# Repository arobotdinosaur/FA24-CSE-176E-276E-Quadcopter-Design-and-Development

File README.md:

Quadcopters designed by Kaustubh Kanagalekar and Alexander Haken

## Introduction

In this project class, we were challenged to design a printed circuit board (PCB) quadcopter and program it using Arduino software in order to achieve flight. 

The class was broken into multiple smaller milestones- PCB design for electronic components, PCB design for quadcopter, sensor filtering and calibration, Proportional, Integral, Derivative (PID) tuning, PCB quadcopter assembly, and flight. As we were designing the PCB quadcopter using computer software, we were provided with a test flight control board (FCB) that we could work on concurrently. We could use either the FCB or the custom PCB quadcopter for demonstration purposes. 

The skills that we learned from the class were-
1. PCB design and fabrication
2. Embedded systems programming 
3. Control theory and sensor calibration 

## Electronic Design

Using Fusion 360, we were tasked with designing the following components from scratch- 

1. Resistor (0805 0Ohm) 
2. Red LED 
3. MOSFET (N-channel) 
4. Inertial measurement unit (IMU) (LSM6DSOXTR 6-Axis) 

We referenced the data sheets for each component online and extensively studied the footprints. 
More specifically, we utilised the footprints tab in Fusion 360 to add SMD pads, silkscreens, keepouts, etc. to accurately replicate the dimensions. 

We also took advantage of the automated building tool at times to accurately build the electronic components.  

Footprint of the resistor

Footprint of the LED 

Footprint of the MOSFET 

Footprint of the IMU 

After creating the footprints, we built symbols for each electronic component using the standard IEEE styling conventions using the symbols tab. 

Finally, we connected the footprints and the symbols of each component in the components tab so that we could use them in our quadcopter schematic and design. 

We ensured that we met all the necessary guidelines and requirements set forth by the PCB manufacturer and instructor in our designs.  

## Quadcopter Design 

We were tasked with creating the schematic for the PCB quadcopter. In addition to our custom made components, we were also provided with additional parts from the instructor. 
The quadcopter had multiple smaller sketches- 
1. The microcontroller connections  
2. Bootloader 
3. IMU 
4. Debug/Rescue Header 
5. Motor Driver 
6. Netbridge and power supply 

### Microcontroller connections
We connected various pins and components to the microcontroller. The most significant connection we had was the balun (used for allowing balanced and unbalanced lines to be interfaced without major disturbances in impedances). This was significant as it allowed us to securely connect the antenna in our design. We were deliberate in our antenna placement as incorrect placements would yield spotty data transmission, and the quadcopter may not be able to fly.  

### Bootloader 
The primary objective of including the bootloader was  to load code to the microcontroller. Pins were connected to the microcontroller from the bootloader. 

### IMU 
We established a communication protocol with the microcontroller using I2C (Inter-Integrated Circuit). We incorporated two wires (Serial Data Line and Serial Clock Line) to transmit data between the microcontroller and IMU. 

### Debug/Rescue Header 
The rescue header was incorporated in order to help with debugging signals during testing. We also added a IMU reuse header in case our soldered IMU had issues. 

### Motor Driver 
We built four copies of the motor driver sketch as there were four motors driving the quadcopter. We included motor pads, mosfets, and a diode in the sketch. More importantly, we also included a decoupling capacitor to help absorb switching noise from the motors.

### Netbridge and Power Supply 
We designed a low-dropout voltage regulator in the schematic to provide a stable power output of 3V to the motors. This was because the batteries were providing power ranging from 4V to 5V. We had two power rails: An unregulated power rail (called VBAT) that provides power to the motors and input of the voltage regulator and is driven directly by the battery, and a regulated supply driven by the voltage regulator (called 3V) 

A netbridge was also created in order to electrically connect two nets in a schematic while keeping the nets separate in schematic . This was done to connect digital ground (BAT_GND) to regular ground. 

Image of the overall schematic 

### PCB Design 
We created a custom shape for the quadcopter and placed all the necessary components from the sketch to the board. The placement of some components were extremely important- for example, the antenna had to be placed near the edge of the board for uninterrupted communication, and the IMU had to be placed at the centre for accurate measurements. The crystal was placed close to the microcontroller, and the motor controllers were placed at the edges of the board. 

We primarily used the autorouter to route all wirings and connections, except in the case of the antenna and parts of the microcontroller. The antenna had to be connected with a large wire (50 mm) manually to the balun and other components (such as the corresponding  microcontroller pins and capacitors). The crystal also had to manually routed with specific pins of the microcontroller. We utilized differential pairs for sending the signals from the antenna and crystal back to the microcontroller due to the sensitivity of these components.

The board had to fit under a 13.9 cm square requirement  with motor holes of 12.2 mm for optimal placement. 
In Fusion 360, the board was aligned to a 1 mm grid for aesthetic reasons. 

We had four layers on the board in order to manage all the wirings and connections succinctly. We had a top layer, bottom layer, and two internal layers (one for 3V/VBAT and the other for GND/BAT_GND). The top and bottom layers involved signal routing for connecting various electronic components. The bottom plan was used whenever possible to reduce electrical noise. The 3V/VBAT and GND/BAT_GND layers were exclusively used for delivering power and ground signals, respectively. The traces that carried both power and ground signals were as short as possible to provide a low-resistance path for current to flow. 
We took care to leave a gap in all the layers beneath the IMU as the manufacture specified that we should not have metal underneath it for best performance.
 
Image of the connected boards in Fusion 360.

## Sensor Filtering and Calibration 

Prior to reading data from the IMU, we had to establish a connection between a test remote and the FCB; we accomplished this using a check-sum that would transmit data sent from the remote (such as throttle value, pitch, roll, yaw) to the FCB. In addition, we also wrote code that read the existing gimbal value from the remote and transmitted it to the FCB to achieve flight. 
The check-sum was created in order to prevent bad data packets from getting sent over and to only accept packets that were sent from our remote (and not from other groups). 

On the FCB, we had to read data from the IMU to accurately measure the orientation. We used an existing library corresponding to the IMU called Adafruit_AHRS- from this, we used the `Adafruit_Simple_AHRS::getQuadOrientation()` function to gather all the necessary data.
We obtained the pitch rate, roll, and yaw from the quad orientation function.  
After gathering these data from the IMU, we created a complementary filter to filter out some of the noise created by the accelerometer and gyroscope. The accelerometer (Euler angles of the orientation) and gyroscope readings (the angular accelerations) were taken from the IMU. 
The reason we created a complementary filter was to gather the best possible data from both the gyroscope and the accelerometer as each inertial sensor has positives and drawbacks. The accelerometers do not drift over time, but they are quite noisy when the motors are running, and slightly less responsive compared to the gyroscope. Whereas, gyroscopes are less noisy than  the accelerometers, but the resulting measurement will drift over time due to accumulated error. We tried to set a high gain such that we could extract more data from the gyroscope in our code. 
We used a standard formula shown below with a gain of 0.98- `cf_angle = (gain) * (cf_angle + (gyro_raw * RAD_TO_DEG * dt)) + (1-gain) * (acc_angle)`

`RAD_TO_DEG = 57.295779513082320876798154814105`
`cf_angle` is the angle resulted from the complementary  filter, `gyro_raw` is the gyroscope measurement, `acc_angle` is the Euler angles, `dt` is the change in time from the measurements.  

We also accounted for any offsets caused by the IMU in the code to have it read zero when levelled. 
We only performed complementary filtering on the roll and pitch axes. 

## PID Control and Tuning 
PID is a type of controller used in feedback systems to regulate speed, position, and various other parameters to ensure stability. We used PID to keep the FCB stable and levelled when the motors were running. 
Proportional (P) responds to the current error and provides immediate action 
Integral (I) accumulates past errors 
Derivative (D) predicts future errors based on the rate of change. 
This was implemented for the pitch and roll axes using the following equation- 
`PID = (Kp* error) + Ki* integral - Kd* derivative` 
Where `Kp, Ki, Kd` are constants that are determined by testing, `error` is the difference from the remote gimbal input and the offset of the axis (`error = setpoint - corrected`), `integral` is `integral = error* dt+integral` , and derivative is the raw gyro readings in degrees. We used the raw gyro readings rather than doing a numerical derivative of cf_pitch because the raw gyroscope readings had slightly less delay. 

PID for yaw rate was implemented a bit differently. The control was only proportional to on the velocity error in yaw, which we got directly from the raw gyroscope yaw data.

After writing the code for all three axes control, we combined them so that there would be an equal output to the motors. We implemented a mixing function which increased the power for the front motors and decreased the power for the rear motors based on the PID output.

Through trial and error, we were able to find the optimal `Kp, Ki, Kd` values for the various axes to achieve stability. For pitch and roll: a ‘P’ overshoot would have resulted in the FCB “sway” from one end to another, an ‘I’ overshoot would have resulted in levelling at an odd angle, and a ‘D’ overshoot would have resulted in the FCB oscillating rapidly. Undershoots of each would have resulted in the quad not being able to move at all. For yaw rate, overshoots of ‘P’ and ‘D’ resulted in the FCB spinning uncontrollably in space, whereas undershoots would have not caused any motion. 

One critical factor for having reliable PID control was having a fast control loop running on the microcontroller. We initially had issues with "derivative kick" where the derivative term was causing unstable behavior due to a high control latency. To optimize speed, we made sure that only critical processes were running. Once we commented out all the print statements that we'd been using for debugging, the loop time reduced from about 35 ms to only 8 ms, and our PID controller ran much better.

For determining the yaw rate coefficients, our control was proportional to the yaw rate error (thus we did not have a `Kd` value after testing).  

This is a video of the PID demonstration for the pitch axis

## PCB Assembly 
After our PCB quadcopter boards were manufactured, we started on the assembly portion of the board. We applied solder paste to our boards using a stencil (a thin aluminium sheet with precise holes corresponding to the board). Immediately after, we attached all the necessary electronic components by hand, ensuring accuracy and precision. We later used a reflow oven to connect the components and the PCB pads as a reflow oven guarantees a secure connections between the paste applied to the PCB pads and the attached components. 
 
Picture of assembly after reflow (note that some components were missing due to unavailability at the time of assembly) 

## Flight 
We demonstrated flight using the provided FCB. 

Flight was broken into the following categories- 
1. "Roombaing" -- moving around the the floor with dowels installed with direction control and minimal yaw
2. Repeated, vertical hopping (>1 inches, > 0.25 second)
3. Repeated, vertical hopping (>6 inches, > 1 second)
4. Repeated, vertical hopping (>12 inches, > 3 seconds)
5. Short flight (>12 inches, > 6 seconds)
6. Sustained flight (> 12 inches, > 10 seconds, demonstrate yaw control)
7. 	Sustained flight (Fly long enough to consume an entire battery)

In this phase, we had also implemented a “trimming” mechanism where we would manually offset any discrepancies in pitch and roll to ensure a level flight takeoff. We would test which direction the FCB would travel towards when throttle was applied and would adjust any errors according. Trimming would have to be done every time we flew from a different location as ground would be levelled differently at each location. 

In our final demonstration, we were able to achieve FL 5. 

Please download the video after clicking the "?" icon to view the flight

## Acknowledgements
We would like to thank our instructor, Dr. Steven Swanson, our TA, Zifeng Zhang, and our classmates for their assistance and guidance with the project.  
Here is the [link](https://github.com/NVSL/QuadClass-Resources) to the main quadcopter class repository.

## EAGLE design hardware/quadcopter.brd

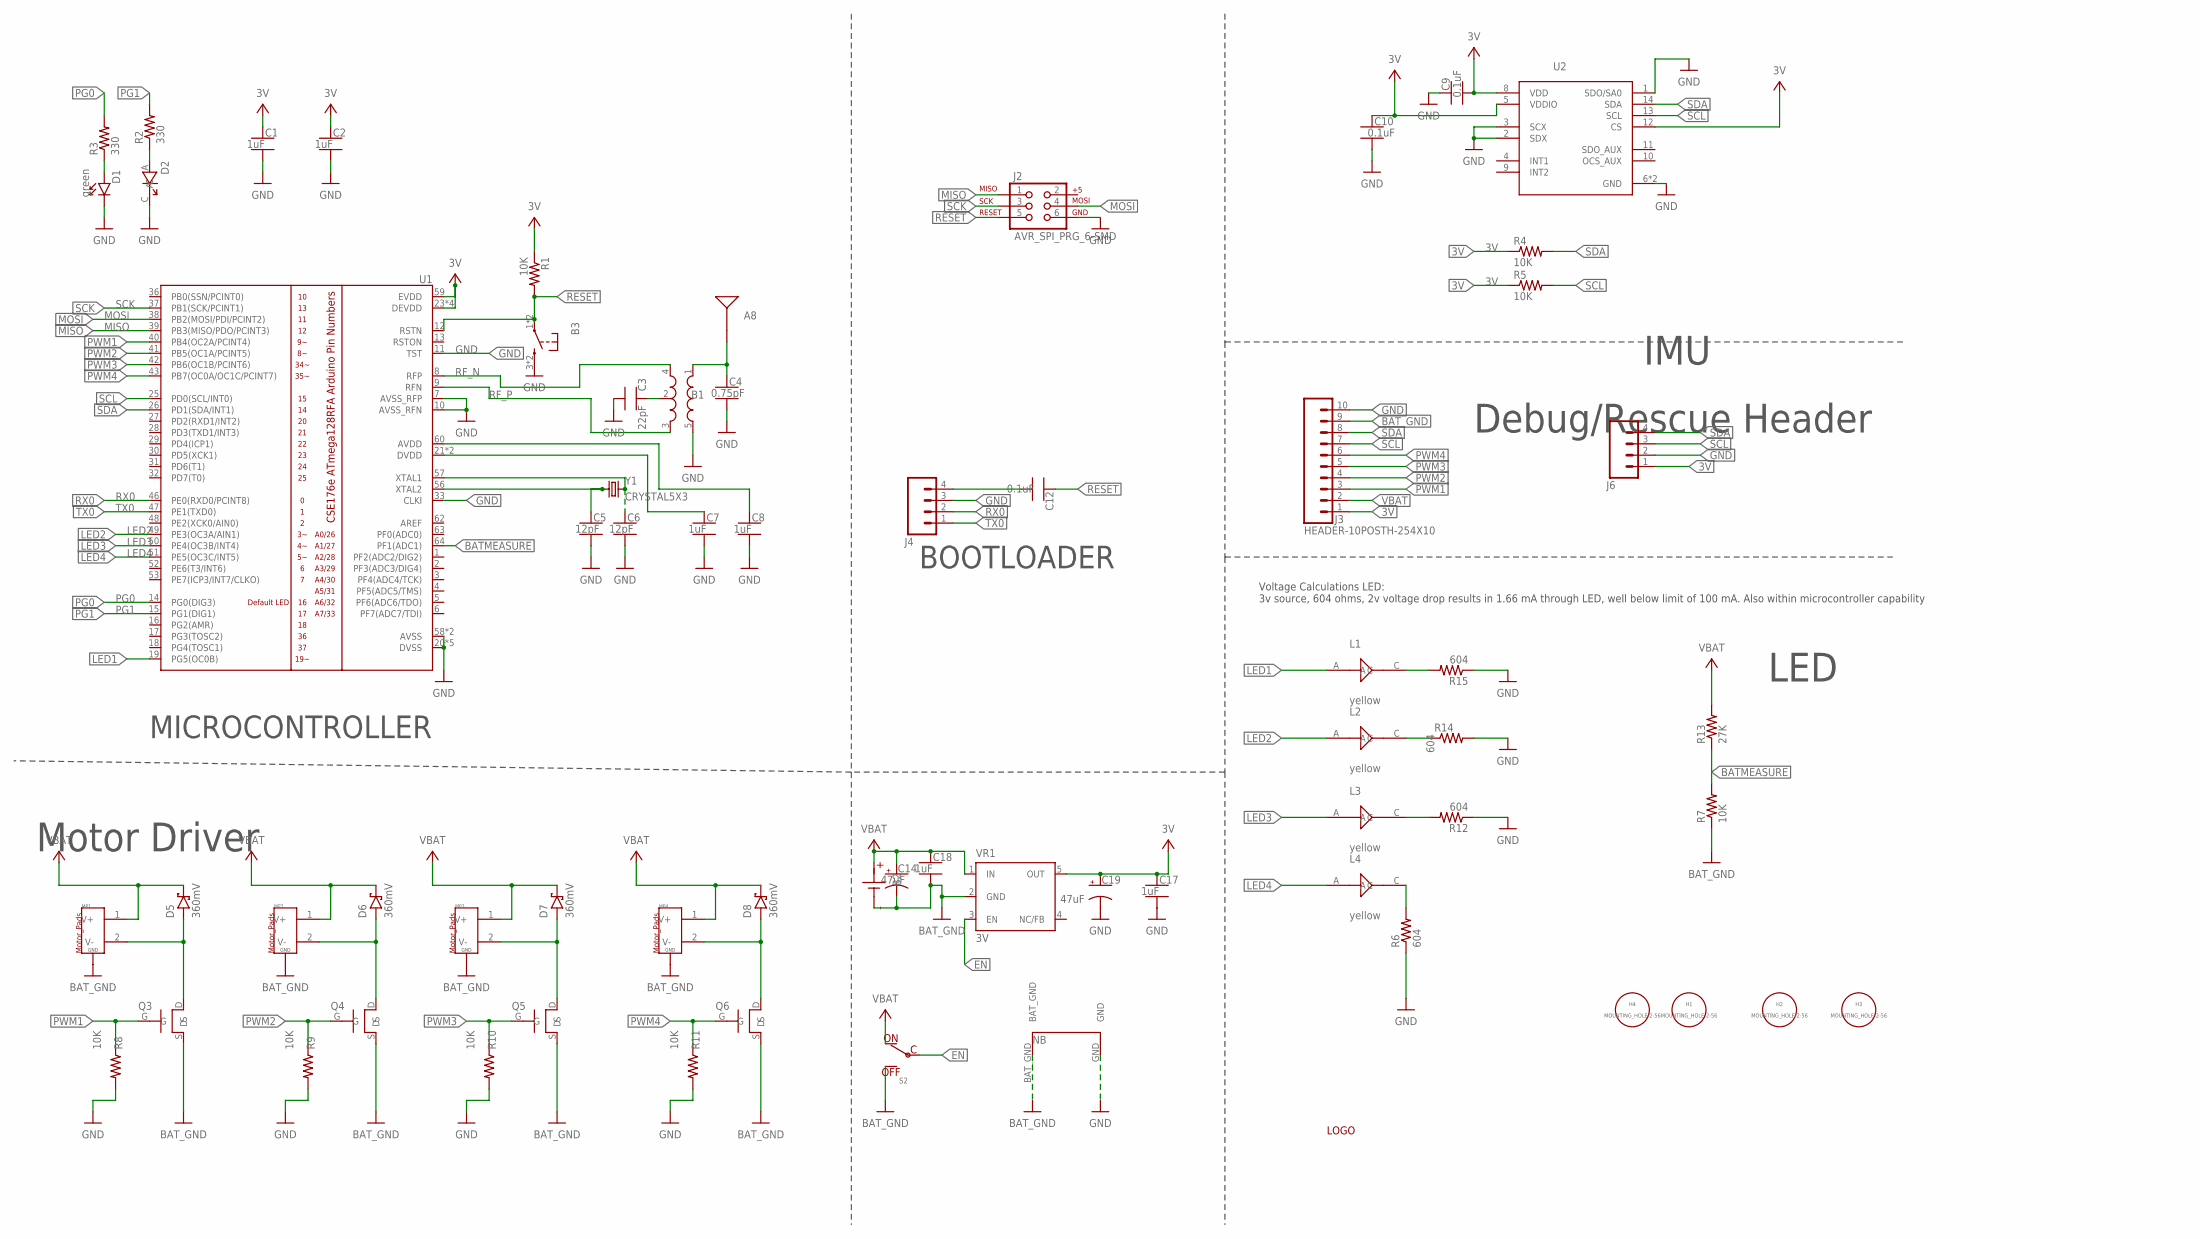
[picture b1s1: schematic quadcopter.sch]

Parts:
A8: ANTENNA-BOARD; ANT_PCB_2.4GHZ_NRF8001_1.6MM_1OZ
B1: BALUN0805; BALUN
B2: BATTERY-SCREW-TERMINAL; SCREW-TERMINAL-1X2-2.54MM
B3: PUSHBUTTON_SMD-VERTICAL-1; TE_FSM8JSMA_HS
C1, C2, C7, C8, C17, C18: 1uF; CAPC2012X140_HS
C3: 22pF; CAPC2012X140_HS
C4: 0.75pF; CAPC2012X140_HS
C5, C6: 12pF; CAPC2012X140_HS
C9, C10, C12: 0.1uF; CAPC2012X140_HS
C14, C19: 47uF; CAPMP3216X180
D1: green; LEDSC125X200X120-2_HS
D2: LED-RED-160-1178-1-ND; LED_160-1178-1-ND
D5, D6, D7, D8: 360mV; SODFL3516X96
H1, H2, H3, H4: MOUNTING_HOLE-2-56; 2-56-MOUNTING-HOLE-NO-METAL
J2: AVR_SPI_PRG_6-SMD; 2X3-SMD
J3: HEADER-10POSTH-254X10; HDRV10W63P254_10X1_2540X254H838_HS
J4: HEADER-4POS-0.1IN-FEMALE-SMD-BOTTOM-ENTRY; HEADER-1X4-BOTTOM-ENTRY
J6: HEADER-4POS-0.1IN-FEMALE; HDRVR4W80P254_1X4_1066X254X850B
L1, L2, L3, L4: yellow; LEDC1507X80NYELLOW
LOGO: PIDLOGO
MP1, MP2, MP3, MP4: MOTOR_PADS_GND-MOLEX-SMD; MOLEX-0532610271
NB: NETBRIDGE
Q3, Q4, Q5, Q6: MOSFET-FET-SI2302CDS-T1-E3CT-NDSI2302CDS-T1-E3CT-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; MOSFET_FET_SI2302CDS-T1-E3CT-ND
R1, R4, R5, R7, R8, R9, R10, R11: 10K; RESC2012X60_HS
R2, R3: 330; RESC2012X60_HS
R6, R12, R14, R15: 604; RESC2012X60_HS
R13: 27K; RESC2012X60_HS
S2: POWER-SWITCH-MFS201N-9-Z-SMD-EDGE; JS102011SAQN
U1: ATMEGA128RFA1; QFN-64
U2: IMU-LSM6DSOXTR-497-18367-1-ND497-18367-1-ND; LSM6DS0
VR1: 3V; SOT23-DBV
Y1: CRYSTAL5X3; CRYSTAL-SMD-5X3

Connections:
3V: C1.1, C2.1, C9.2, C10.1, C17.1, C19.1 (+), J3.1, J6.1, R1.1, R4.1, R5.1, U1.23 (DEVDD), U1.34 (DEVDD), U1.44 (DEVDD), U1.54 (DEVDD), U1.59 (EVDD), U2.5 (VDDIO), U2.8 (VDD), U2.12 (CS), VR1.5 (OUT)
BATMEASURE: R7.2, R13.1, U1.64 (PF1(ADC1))
BAT_GND: B2.1 (N), C14.2 (-), C18.2, J3.9, MP1.G1 (GND), MP1.G2 (GND), MP2.G1 (GND), MP2.G2 (GND), MP3.G1 (GND), MP3.G2 (GND), MP4.G1 (GND), MP4.G2 (GND), NB.BAT_GND, Q3.S, Q4.S, Q5.S, Q6.S, R7.1, S2.A (OFF), VR1.2 (GND)
EN: S2.C, VR1.3 (EN)
GND: B1.5 (GND), B3.3 (2), B3.4 (2), C1.2, C2.2, C3.2, C4.2, C5.2, C6.2, C7.2, C8.2, C9.1, C10.2, C17.2, C19.2 (-), D1.C, D2.C, J2.6, J3.10, J4.3, J6.2, NB.GND, R6.1, R8.2, R9.2, R10.2, R11.2, R12.1, R14.2, R15.1, U1.7 (AVSS_RFP), U1.10 (AVSS_RFN), U1.11 (TST), U1.20 (DVSS), U1.24 (DVSS), U1.33 (CLKI), U1.35 (DVSS), U1.45 (DVSS), U1.55 (DVSS), U1.58 (AVSS), U1.61 (AVSS), U2.1 (SDO/SA0), U2.2 (SDX), U2.3 (SCX), U2.6 (GND), U2.7 (GND)
LED1: L1.A, U1.19 (PG5(OC0B))
LED2: L2.A, U1.49 (PE3(OC3A/AIN1))
LED3: L3.A, U1.50 (PE4(OC3B/INT4))
LED4: L4.A, U1.51 (PE5(OC3C/INT5))
MISO: J2.1, U1.39 (PB3(MISO/PDO/PCINT3))
MOSI: J2.4, U1.38 (PB2(MOSI/PDI/PCINT2))
unnamed: D1.A, R3.1
unnamed: D2.A, R2.1
unnamed: B1.2 (GND), C3.1
unnamed: A8.FEED, B1.1 (IN), C4.1
unnamed: C8.1, U1.60 (AVDD)
unnamed: C7.1, U1.21 (DVDD), U1.22 (DVDD)
unnamed: C6.1, U1.57 (XTAL1), Y1.3 (2)
unnamed: C5.1, U1.56 (XTAL2), Y1.1
unnamed: L1.C, R15.2
unnamed: C12.2, J4.4
unnamed: L4.C, R6.2
unnamed: L2.C, R14.1
unnamed: L3.C, R12.2
unnamed: D5.2 (A), MP1.2 (V-), Q3.D
unnamed: D6.2 (A), MP2.2 (V-), Q4.D
unnamed: D7.2 (A), MP3.2 (V-), Q5.D
unnamed: D8.2 (A), MP4.2 (V-), Q6.D
PG0: R3.2, U1.14 (PG0(DIG3))
PG1: R2.2, U1.15 (PG1(DIG1))
PWM1: J3.3, Q3.G, R8.1, U1.40 (PB4(OC2A/PCINT4))
PWM2: J3.4, Q4.G, R9.1, U1.41 (PB5(OC1A/PCINT5))
PWM3: J3.5, Q5.G, R10.1, U1.42 (PB6(OC1B/PCINT6))
PWM4: J3.6, Q6.G, R11.1, U1.43 (PB7(OC0A/OC1C/PCINT7))
RESET: B3.1, B3.2 (1), C12.1, J2.5, R1.2, U1.12 (RSTN)
RF_N: B1.4 (OUT1), U1.8 (RFP)
RF_P: B1.3 (OUT2), U1.9 (RFN)
RX0: J4.2, U1.46 (PE0(RXD0/PCINT8))
SCK: J2.3, U1.37 (PB1(SCK/PCINT1))
SCL: J3.7, J6.3, R5.2, U1.25 (PD0(SCL/INT0)), U2.13 (SCL)
SDA: J3.8, J6.4, R4.2, U1.26 (PD1(SDA/INT1)), U2.14 (SDA)
TX0: J4.1, U1.47 (PE1(TXD0))
VBAT: B2.2, C14.1 (+), C18.1, D5.1 (C), D6.1 (C), D7.1 (C), D8.1 (C), J3.2, MP1.1 (V+), MP2.1 (V+), MP3.1 (V+), MP4.1 (V+), R13.2, S2.B (ON), VR1.1 (IN)

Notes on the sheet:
BOOTLOADER
MICROCONTROLLER
Voltage Calculations LED: 3v source, 604 ohms, 2v voltage drop results in 1.66 mA through LED, well below limit of 100 mA. Also within microcontroller capability
Motor Driver
LED
Debug/Rescue Header
IMU

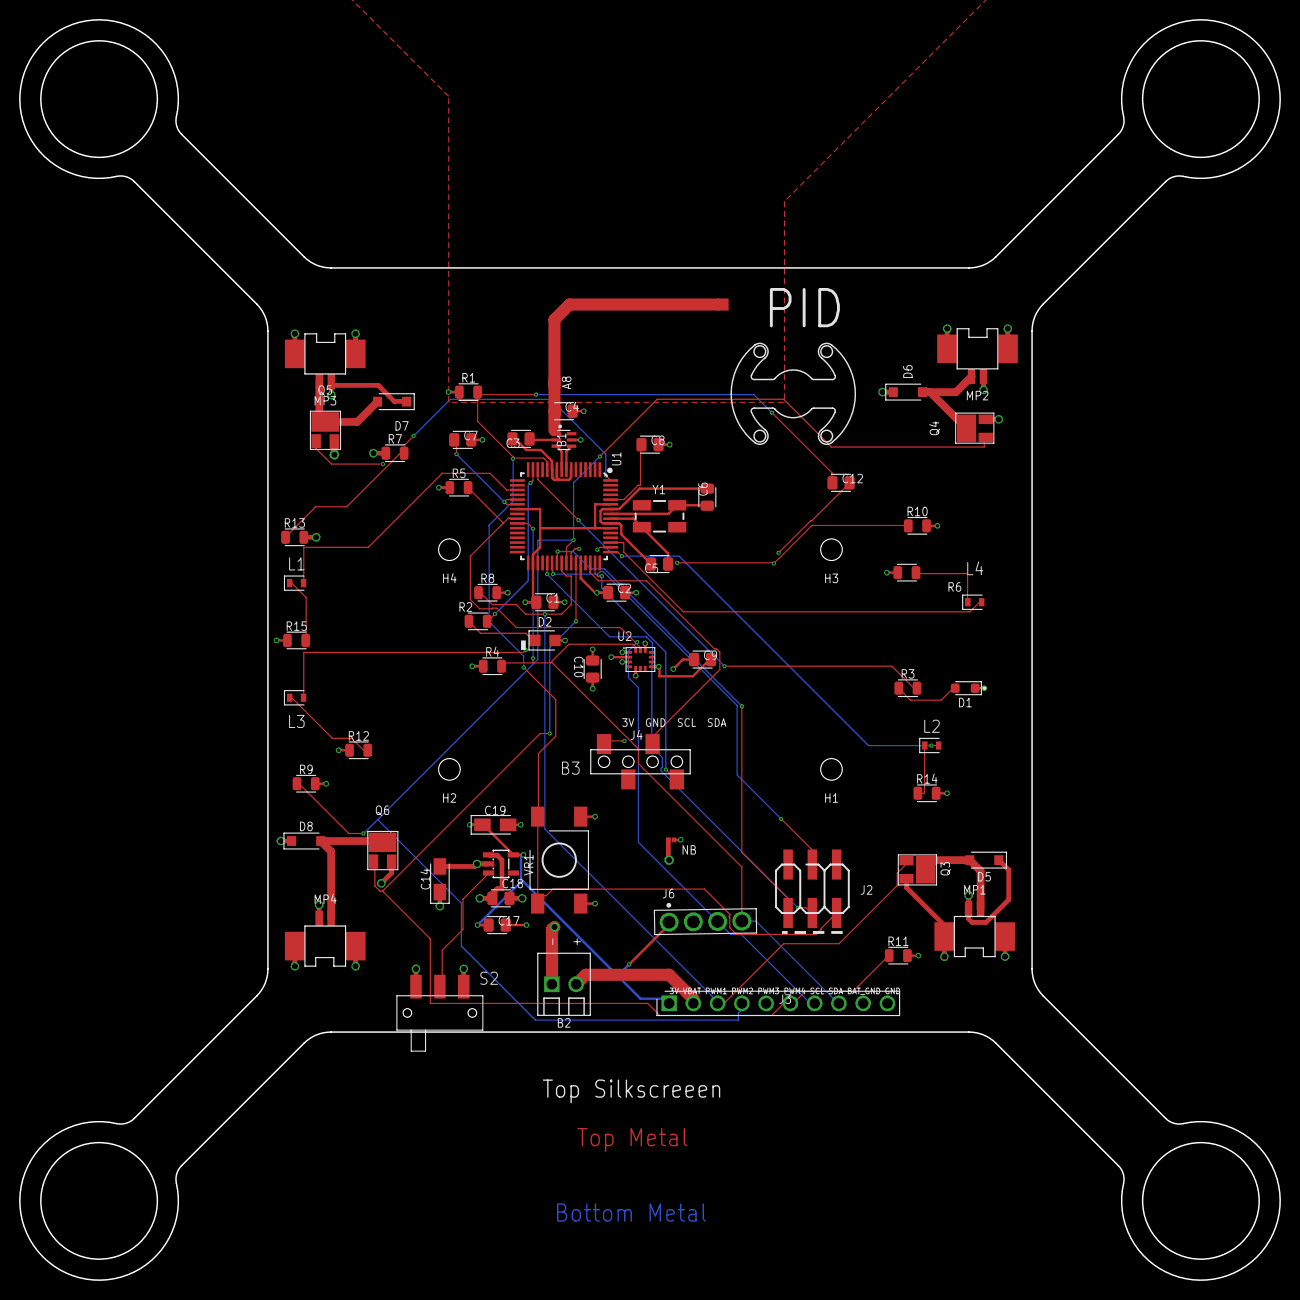
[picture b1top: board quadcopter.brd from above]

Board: 4 copper layers, 132.0 x 132.0 mm, 68 parts (0 on the bottom side), 43 nets.

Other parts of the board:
U$1: LAYER_LABELS

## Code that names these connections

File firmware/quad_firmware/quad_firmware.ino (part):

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  analogReference(INTERNAL);

  // global declaration of LEDs 
  const int LED1 = 16;
  const int LED2 = 17; 
  const int LED3 = 18; 
  const int LED4 = 36; 
  const int PRETTY_LEDS = 34;

  //startupRamp(); 
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
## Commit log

2024-10-08 test
2024-10-08 fixed submodule
2024-10-08 add quad and remote firmware
2024-10-10 starting to try to read gimbals, A1,2,3 work but A0 is weird
2024-10-10 updated gimble reading
2024-10-10 updated file
2024-10-10 battery
2024-10-11 edited quad_firmware.ino
2024-10-12 this is hard
2024-10-12 changed quad fw ino
2024-10-12 extra code
2024-10-12 partial code for calibration
2024-10-13 radio control of throttle works
2024-10-14 print hi
2024-10-14 calibration for throttle only, not saved yet
2024-10-14 calibration for throttle only, now saved to EEPROM
2024-10-14 rudimentary arming kind of works
2024-10-15 still faulty issues with data packet
2024-10-15 fixed quadcopter freaking out on calibration issue
2024-10-15 with right updown calibration
2024-10-15 calibration for all 4 axes
2024-10-15 added LED when armed, disarm function, stopped risk of quadcopter timing increment overflow
2024-10-15 quadcopter sends battery to remote, remote displays both batteries, battery % shown, remote disarms upon losing quadcopter connection, LED displays connection status, only issue is the remote disarms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
2024-10-15 fixed typo in calibration
2024-10-15 the best we've got so far
2024-10-16 experimented with packet length verification
2024-10-16 schematic
2024-10-16 custom is Kaustubh's electronic component file
2024-10-17 the interference situation is improved by reading all the packets that come in and parsing that for a valid packet. But it still fails in high-noise
2024-10-17 test of schematic
2024-10-18 library
2024-10-19 check issue with code for data acq and graph
2024-10-19 issues but tried to fix some plotting issues
2024-10-19 no compilation issues for emu data pitch and pitch rate
2024-10-20 added code for complementary filtering (Filtering in Software part of lab)
2024-10-20 addon
2024-10-20 complementary filtering in comments
2024-10-20 moving schematic for eaglint
2024-10-21 battery voltage
2024-10-21 debugging disconnect issues, without much success yet
2024-10-21 fixing many eaglint errors, mostly disconnected nets
2024-10-21 led updates and minor fixes, like reconnecting bad labels
2024-10-21 can now successfully filter interference from other channels, but not on the same channel yet. At least no more crashing, even with interference on the same channel
2024-10-21 see what new issues we have
2024-10-21 datasheets
2024-10-21 a few less errors
2024-10-21 fixing voltage regulator/switch
2024-10-22 please work
2024-10-22 fixed issues with sensor outputs
2024-10-22 working?
2024-10-22 lets see what needs to be fixed
2024-10-22 fixed power supply stuff, a lot of broken led nets, still havent found N...
2024-10-22 fixing library issues mostly, also a netbrige error, stil cant find N
2024-10-22 fixing LED values, more library dependencies
2024-10-22 swap out battery
2024-10-22 fix missing net in schematic
2024-10-22 packet debugging
2024-10-24 fixing quadcopter schematic
2024-10-24 fixing imu rescue header
2024-10-24 firmware
2024-10-29 check, lots of work from both of us
2024-10-29 update schematic
2024-10-31 fixing many issues from quick check
2024-10-31 ready for full check, fixed last few trivial issues
2024-11-01 fixed a bunch of routing issues/vias, added logo
2024-11-01 fixed high-current net issues
2024-11-01 removed invisible net
2024-11-02 preliminary PID code. Not guaranteed to work as intended
2024-11-02 i really hope this passes
2024-11-02 i really hope this one passes
2024-11-04 pid tweaks+mixing redo+stopped using delay to delay and instead use a millis() count so everything else runs faster
2024-11-05 added pid debugs but not working
2024-11-05 final quadcopter ready for manufacturing
2024-11-05 final manufacturing (hopefully) :)
2024-11-05 :) :D ;)
2024-11-05 final board? :)
2024-11-05 v111
2024-11-05 pid maybe works
2024-11-07 publishing all joystick axes over remote
2024-11-07 edited coeff
2024-11-07 new.x instead of .z
2024-11-07 added some raw code for yaw
2024-11-07 still doesnt work
2024-11-07 no progress
2024-11-07 adding buttons
2024-11-10 kind of works, lots of improvements
2024-11-11 finally hovers reasonably well with pitch
2024-11-11 works for pitch control. Fixed radio overflow issue.
2024-11-12 doesnt work yet but want to save before flight
2024-11-12 yaw kind of works
2024-11-12 fixing radio
2024-11-12 works for pitch+yaw seperately
2024-11-12 ceiling on pid helps with instability
2024-11-13 don't let your dreams become memes like me
2024-11-14 knob and buttons read now but not implemented. very very tired and stressed. long week.
2024-11-14 we're screwed
2024-11-15 bill of materials with parts checked off
2024-11-16 original
2024-11-16 remote controlling quadcopter works. Also we learned timing is important for radio. Kaustubh is the goat
2024-11-17 added rad-to-deg for derivatived, flipped sign so it does what we want, fixed data loss issue when transmitting due to int to float conversion
2024-11-17 added filter to smoothen d, constrains to d,i
2024-11-18 frustrating
2024-11-19 kind of semi works for both pitch+yaw
2024-11-19 changes set
2024-11-21 added yaw button
2024-11-21 working yaw
2024-11-21 now with roll code not fully done
2024-11-23 now you can push the bottom button to level. Also the first attempt at a flying function was made. Right now it is just a flip over onto the floor function
2024-11-29 new mixing algorithm ensures that pid values are fully applied even at 255 throttle
2024-12-01 fix for mixing algorithm
2024-12-02 no clue
2024-12-03 FLIGHT
2024-12-03 fixed pitch+yaw, bizzarely high i change to make it work tonight...
2024-12-03 noise.txt
2024-12-05 trim control from remote added.
2024-12-07 it kind of works, probably as good as its going to get
2024-12-19 Add files via upload
    Miscellaneous Items
